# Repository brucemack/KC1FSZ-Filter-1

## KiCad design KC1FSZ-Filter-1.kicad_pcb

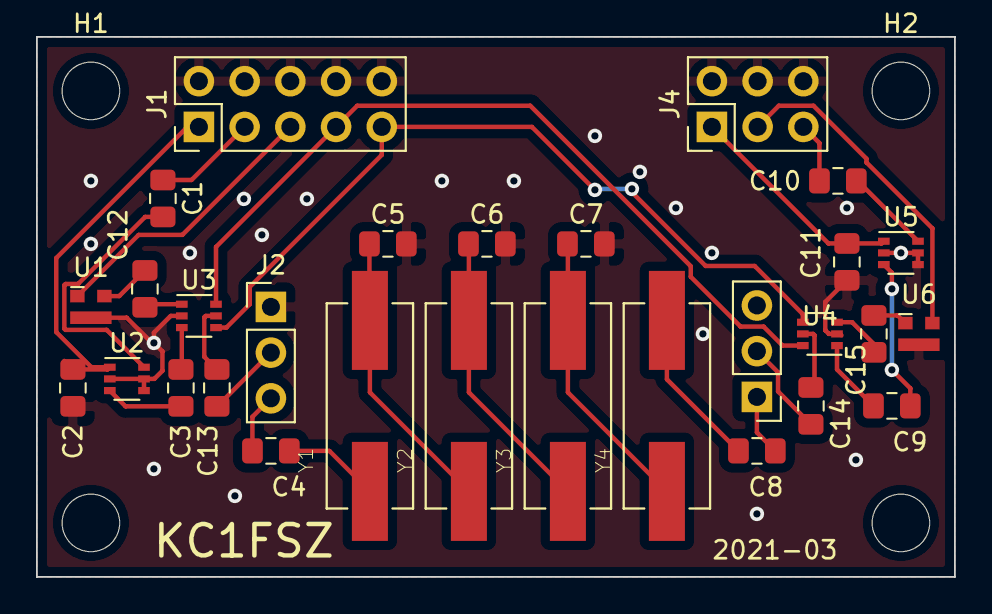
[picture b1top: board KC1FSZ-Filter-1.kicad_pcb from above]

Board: 2 copper layers, 51.0 x 30.0 mm, 33 parts (0 on the bottom side), 30 nets.

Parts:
C1, C2, C3, C9, C10, C11, C12, C13, C14, C15: 0.1U; C_0805_2012Metric_Pad1.15x1.40mm_HandSolder
C4, C5, C6, C7, C8: 100P; C_0805_2012Metric_Pad1.15x1.40mm_HandSolder
H1, H2, H3, H4: MountingHole; MountingHole_3.2mm_M3_ISO14580
J1: Conn_02x05_Odd_Even; PinHeader_2x05_P2.54mm_Vertical
J2, J3: Conn_01x03; PinHeader_1x03_P2.54mm_Vertical
J4: Conn_02x03_Odd_Even; PinHeader_2x03_P2.54mm_Vertical
U1, U6: PAT1220-C-6DB; RF_Attenuator_Susumu_PAT1220
U2, U5: BGA2867; SOT-363_SC-70-6
U3, U4: MASW-007221; SOT-363_SC-70-6
Y1, Y2, Y3, Y4: Crystal; XTAL_ECS-100-18-5P-TR

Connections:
+5VA: C2.1, J1.1, U2.1
+5VD: C11.1, J4.1, U5.1
FILTER_L: C13.2, J2.2
FILTER_R: C14.2, J3.2
GNDA: C2.2, C5.2, C6.2, C7.2, C11.2, J1.2, J1.4, J1.6, J1.8, J1.10, J2.1, J3.3, J4.2, J4.4, J4.6, U1.3, U2.2, U2.4, U2.5, U3.2, U4.2, U5.2, U5.4, U5.5, U6.3
unnamed: C1.2, U2.6
unnamed: C3.1, U3.3
unnamed: C3.2, U2.3
unnamed: C4.1, Y1.1
unnamed: C4.2, J2.3
unnamed: C5.1, Y1.2, Y2.1
unnamed: C6.1, Y2.2, Y3.1
unnamed: C7.1, Y3.2, Y4.1
unnamed: C8.1, J3.1
unnamed: C8.2, Y4.2
unnamed: C9.1, U4.1
unnamed: C9.2, U5.3
unnamed: C10.2, U5.6
unnamed: C12.1, U3.1
unnamed: C12.2, U1.2
unnamed: C13.1, U3.5
unnamed: C14.1, U4.5
unnamed: C15.1, U4.3
unnamed: C15.2, U6.1
RX_IN: C10.1, J4.5
RX_OUT: J1.5, U1.1
SEL1: J1.7, U3.6, U4.6
SEL2: J1.9, U3.4, U4.4
TX_IN: C1.1, J1.3
TX_OUT: J4.3, U6.2

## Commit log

2021-03-24 Ready for RIT
